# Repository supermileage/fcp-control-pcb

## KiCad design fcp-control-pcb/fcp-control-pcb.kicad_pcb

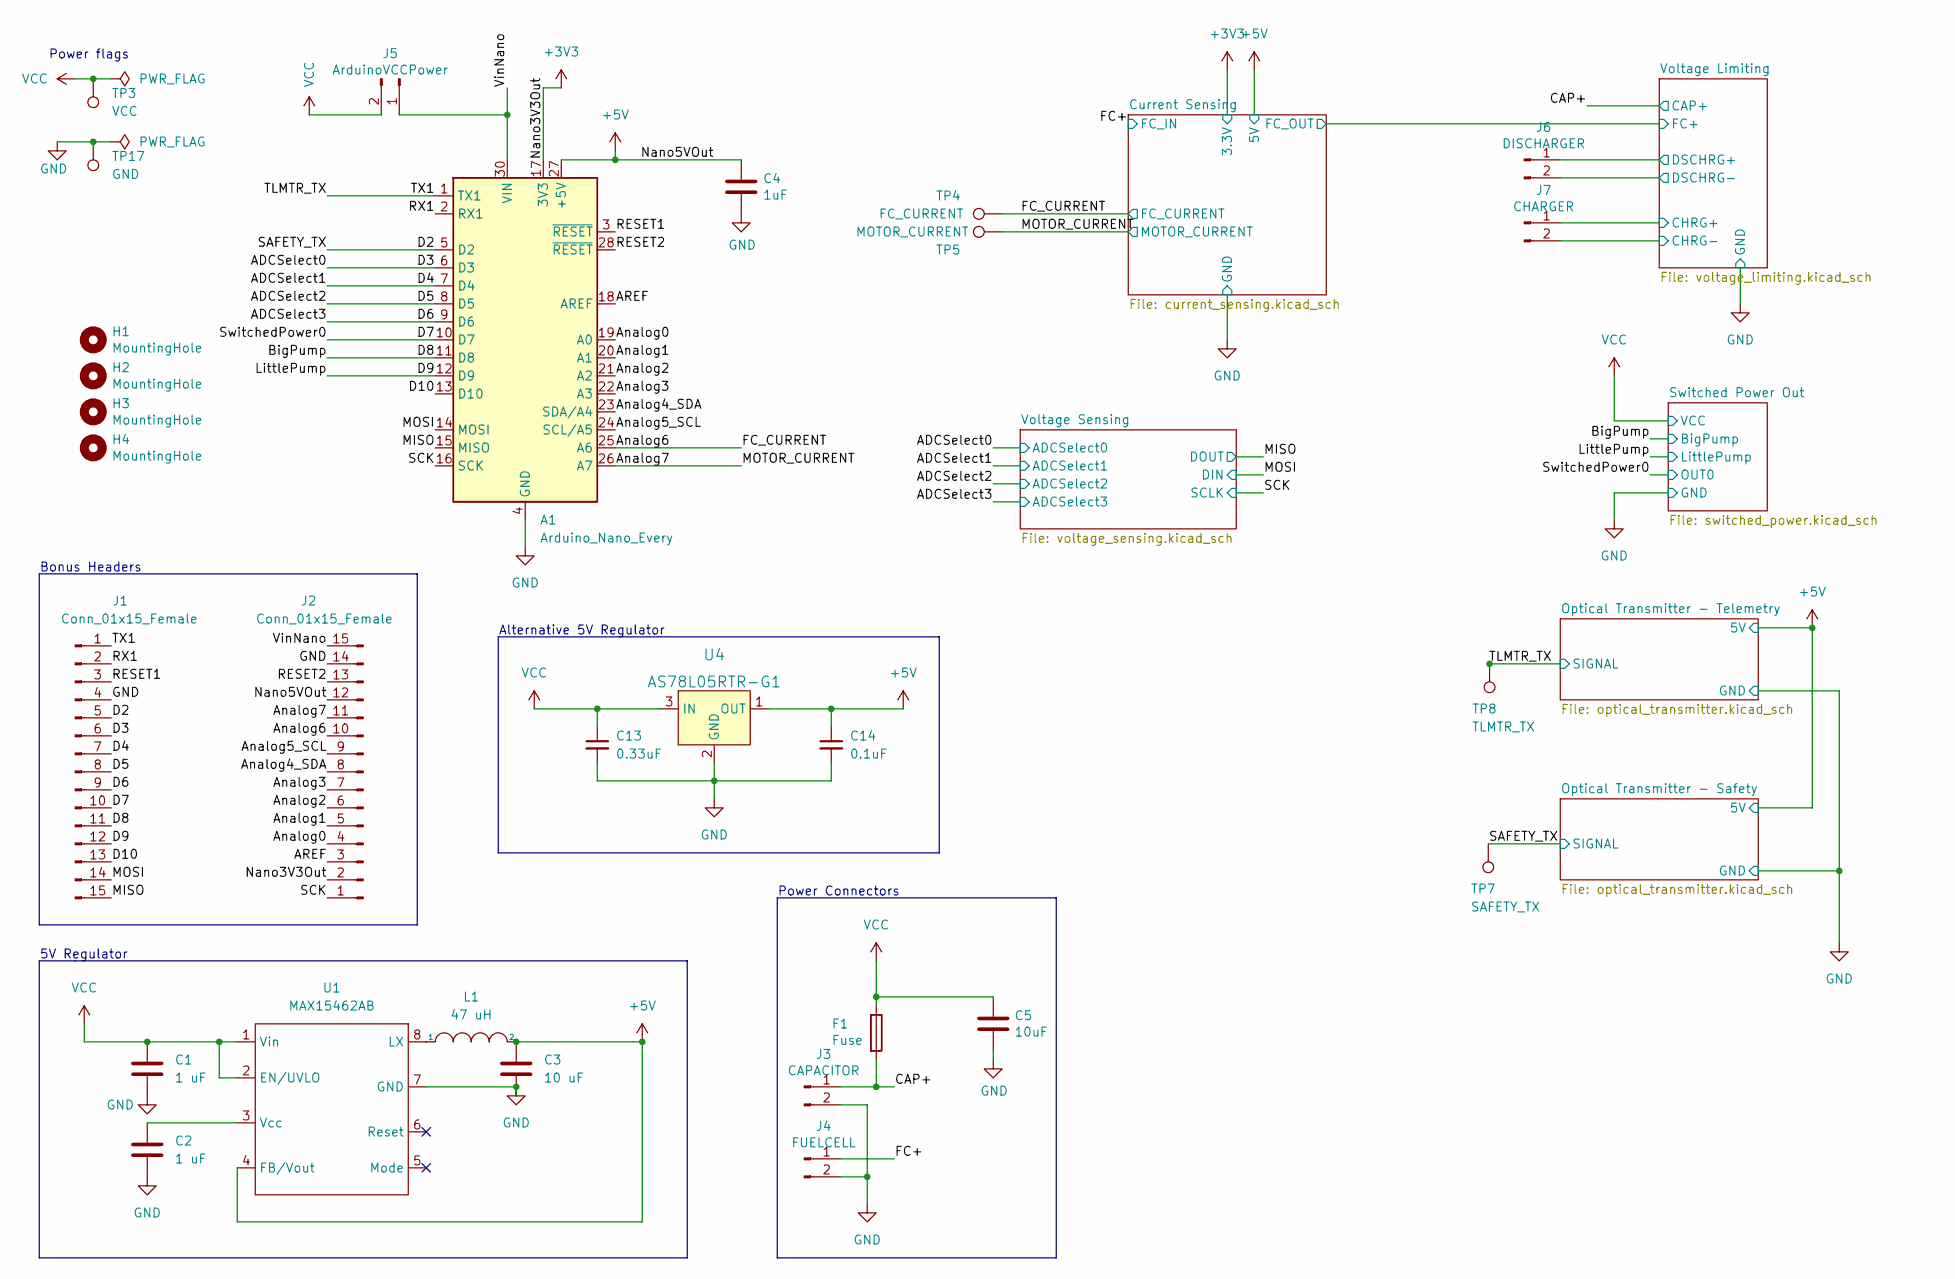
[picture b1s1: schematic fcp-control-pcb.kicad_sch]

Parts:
A1: Arduino_Nano_Every; Arduino_Nano
C1, C2: 1 uF; C_0805_2012Metric_Pad1.18x1.45mm_HandSolder
C3: 10 uF; C_0805_2012Metric_Pad1.18x1.45mm_HandSolder
C4: 1uF; C_0805_2012Metric_Pad1.18x1.45mm_HandSolder; DigikeyPN 490-12330-1-ND
C5: 10uF; C_0805_2012Metric_Pad1.18x1.45mm_HandSolder; DigikeyPN 490-12330-1-ND
C13: 0.33uF; C_0805_2012Metric_Pad1.18x1.45mm_HandSolder
C14: 0.1uF; C_0805_2012Metric_Pad1.18x1.45mm_HandSolder
F1: Fuse; 3586KTR; DigikeyPN 36-3586KCT-ND
H1, H2, H3, H4: MountingHole; MountingHole_3.2mm_M3
J1, J2: Conn_01x15_Female; PinSocket_1x15_P2.54mm_Vertical; MPN 310-87-115-41-001101; DigikeyPN 1212-1103-ND
J3: CAPACITOR; VP0265540000G
J4: FUELCELL; VP0265540000G; DigikeyPN VP0265540000G-ND
J5: ArduinoVCCPower; PinHeader_1x02_P2.54mm_Vertical
J6: DISCHARGER; Molex_Mini-Fit_Jr_5569-02A2_2x01_P4.20mm_Horizontal; DigikeyPN 0050361758-ND
J7: CHARGER; Molex_Mini-Fit_Jr_5569-02A2_2x01_P4.20mm_Horizontal; DigikeyPN 0050361758-ND
L1: 47 uH; L_Coilcraft_LPS4018
TP3: VCC; TestPoint_Pad_4.0x4.0mm
TP4: FC_CURRENT; TestPoint_Pad_4.0x4.0mm
TP5: MOTOR_CURRENT; TestPoint_Pad_4.0x4.0mm
TP7: SAFETY_TX; TestPoint_Pad_4.0x4.0mm
TP8: TLMTR_TX; TestPoint_Pad_4.0x4.0mm
TP17: GND; TestPoint_Pad_4.0x4.0mm
U1: MAX15462AB; TDFN-8-1EP_2x2mm_P0.5mm_EP0.8x1.2mm; digikey part no. MAX15462BATA+TCT-ND
U4: AS78L05RTR-G1; SOT-89-3_Handsoldering; MPN AS78L05RTR-G1; Digi-Key_PN AS78L05RTR-G1DITR-ND

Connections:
+3V3: A1.17 (3V3), J2.2; also elsewhere on the board
+5V: A1.27 (+5V), C3.1, C4.1, C14.1, J2.12, L1.2, U1.4 (FB/Vout), U4.1 (OUT); also elsewhere on the board
/ADCSelect0: A1.6 (D3), J1.6; also elsewhere on the board
/ADCSelect1: A1.7 (D4), J1.7; also elsewhere on the board
/ADCSelect2: A1.8 (D5), J1.8; also elsewhere on the board
/ADCSelect3: A1.9 (D6), J1.9; also elsewhere on the board
/AREF: A1.18 (AREF), J2.3
/Analog0: A1.19 (A0), J2.4
/Analog1: A1.20 (A1), J2.5
/Analog2: A1.21 (A2), J2.6
/Analog3: A1.22 (A3), J2.7
/Analog4_SDA: A1.23 (SDA/A4), J2.8
/Analog5_SCL: A1.24 (SCL/A5), J2.9
/Analog6: A1.25 (A6), J2.10, TP4.1; also elsewhere on the board
/Analog7: A1.26 (A7), J2.11, TP5.1; also elsewhere on the board
/BigPump: A1.11 (D8), J1.11; also elsewhere on the board
/CAP+: F1.2, J3.1; also elsewhere on the board
/D2: A1.5 (D2), J1.5, TP7.1; also elsewhere on the board
/D7: A1.10 (D7), J1.10; also elsewhere on the board
/D9: A1.12 (D9), J1.12; also elsewhere on the board
/D10: A1.13 (D10), J1.13
/FC+: J4.1; also elsewhere on the board
/MISO: A1.15 (MISO), J1.15; also elsewhere on the board
/MOSI: A1.14 (MOSI), J1.14; also elsewhere on the board
/RESET1: A1.3 (~RESET), J1.3
/RESET2: A1.28 (~RESET), J2.13
/RX1: A1.2 (RX1), J1.2
/SCK: A1.16 (SCK), J2.1; also elsewhere on the board
/TLMTR_TX: A1.1 (TX1), J1.1, TP8.1; also elsewhere on the board
/VinNano: A1.30 (VIN), J2.15, J5.1
/Voltage Limiting/CHRG+: J7.1; also elsewhere on the board
/Voltage Limiting/DSCHRG+: J6.1; also elsewhere on the board
GND: A1.4 (GND), A1.29 (GND), C1.2, C2.2, C3.2, C4.2, C5.2, C13.2, C14.2, J1.4, J2.14, J3.2, J4.2, J6.2, J7.2, TP17.1, U1.7 (GND), U4.2 (GND); also elsewhere on the board
unnamed: C2.1, U1.3 (Vcc)
unnamed: L1.1, U1.8 (LX)
VCC: C1.1, C5.1, C13.1, F1.1, J5.2, TP3.1, U1.1 (Vin), U1.2 (EN/UVLO), U4.3 (IN); also elsewhere on the board

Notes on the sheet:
5V Regulator
Power Connectors
Power flags
Bonus Headers
Alternative 5V Regulator

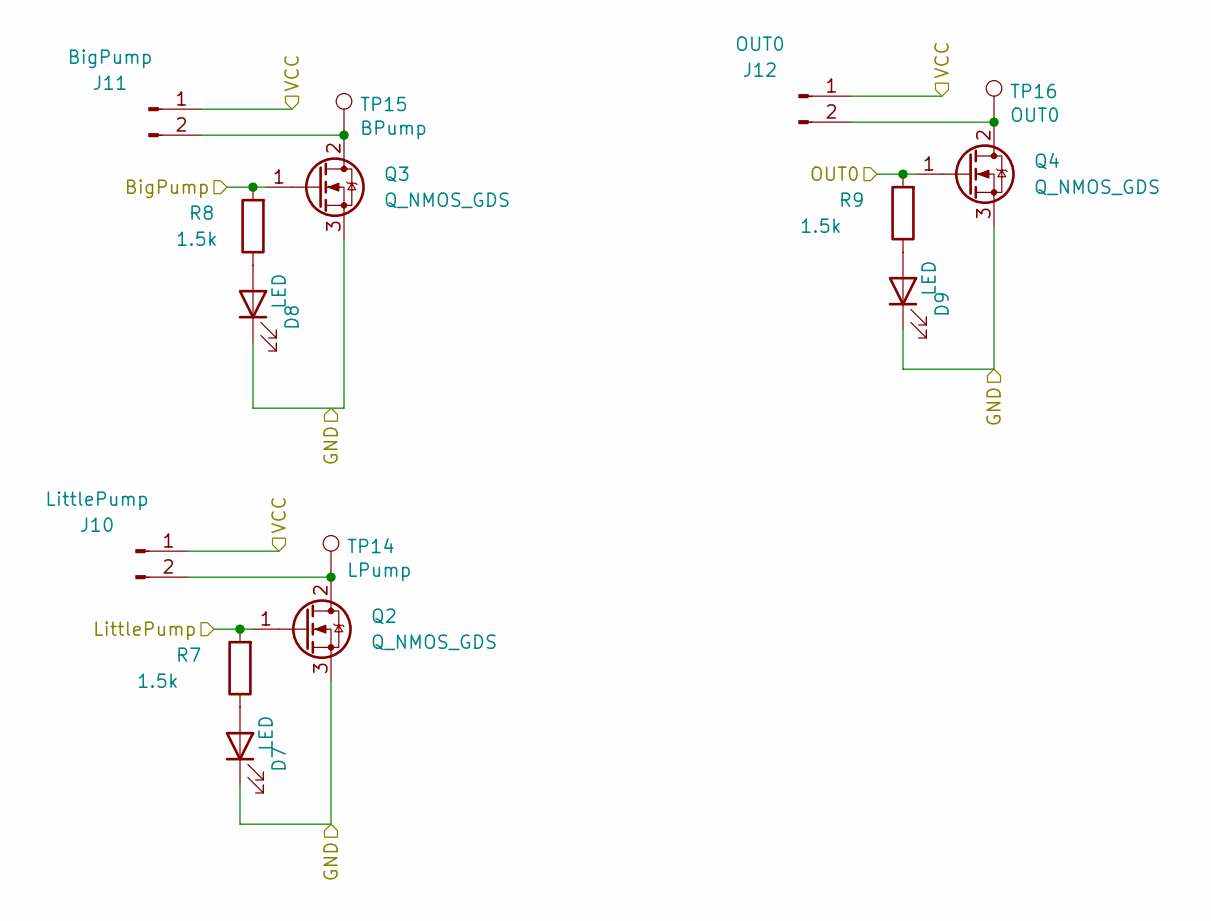
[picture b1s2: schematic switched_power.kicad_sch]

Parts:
D7, D8, D9: LED; LED_0603_1608Metric; DigikeyPN SML-D12W8WT86ACT-ND
J10: LittlePump; Molex_Mini-Fit_Jr_5569-02A2_2x01_P4.20mm_Horizontal; DigikeyPN 0050361758-ND
J11: BigPump; Molex_Mini-Fit_Jr_5569-02A2_2x01_P4.20mm_Horizontal; DigikeyPN 0050361758-ND
J12: OUT0; Molex_Mini-Fit_Jr_5569-02A2_2x01_P4.20mm_Horizontal; DigikeyPN 0050361758-ND
Q2, Q3, Q4: Q_NMOS_GDS; SOT-89-3_Handsoldering; DigikeyPN DMN2004WKDICT-ND
R7, R8, R9: 1.5k; R_0805_2012Metric_Pad1.20x1.40mm_HandSolder; DigikeyPN A121524CT-ND
TP14: LPump; PinSocket_1x01_P2.54mm_Vertical
TP15: BPump; PinSocket_1x01_P2.54mm_Vertical
TP16: OUT0; PinSocket_1x01_P2.54mm_Vertical

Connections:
/BigPump: Q3.1 (G), R8.2; also elsewhere on the board
/D7: Q4.1 (G), R9.2; also elsewhere on the board
/D9: Q2.1 (G), R7.2; also elsewhere on the board
GND: D7.1 (K), D8.1 (K), D9.1 (K), Q2.3 (S), Q3.3 (S), Q4.3 (S); also elsewhere on the board
unnamed: D7.2 (A), R7.1
unnamed: D8.2 (A), R8.1
unnamed: D9.2 (A), R9.1
unnamed: J10.2, Q2.2 (D), TP14.1
unnamed: J11.2, Q3.2 (D), TP15.1
unnamed: J12.2, Q4.2 (D), TP16.1
VCC: J10.1, J11.1, J12.1; also elsewhere on the board

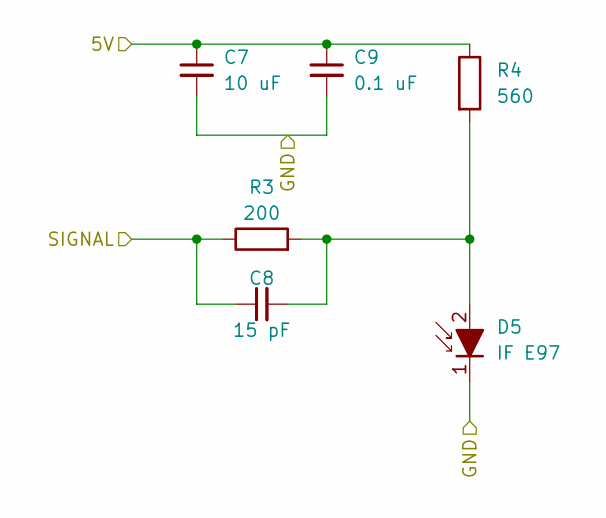
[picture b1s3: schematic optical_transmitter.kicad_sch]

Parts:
C7: 10 uF; C_0805_2012Metric_Pad1.18x1.45mm_HandSolder
C8: 15 pF; C_0805_2012Metric_Pad1.18x1.45mm_HandSolder
C9: 0.1 uF; C_0805_2012Metric_Pad1.18x1.45mm_HandSolder
D5: IF E97; IF-E97
R3: 200; R_0805_2012Metric_Pad1.20x1.40mm_HandSolder
R4: 560; R_0805_2012Metric_Pad1.20x1.40mm_HandSolder

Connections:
+5V: C7.1, C9.1, R4.1; also elsewhere on the board
/TLMTR_TX: C8.1, R3.1; also elsewhere on the board
GND: C7.2, C9.2, D5.1 (K); also elsewhere on the board
unnamed: C8.2, D5.2 (A), R3.2, R4.2

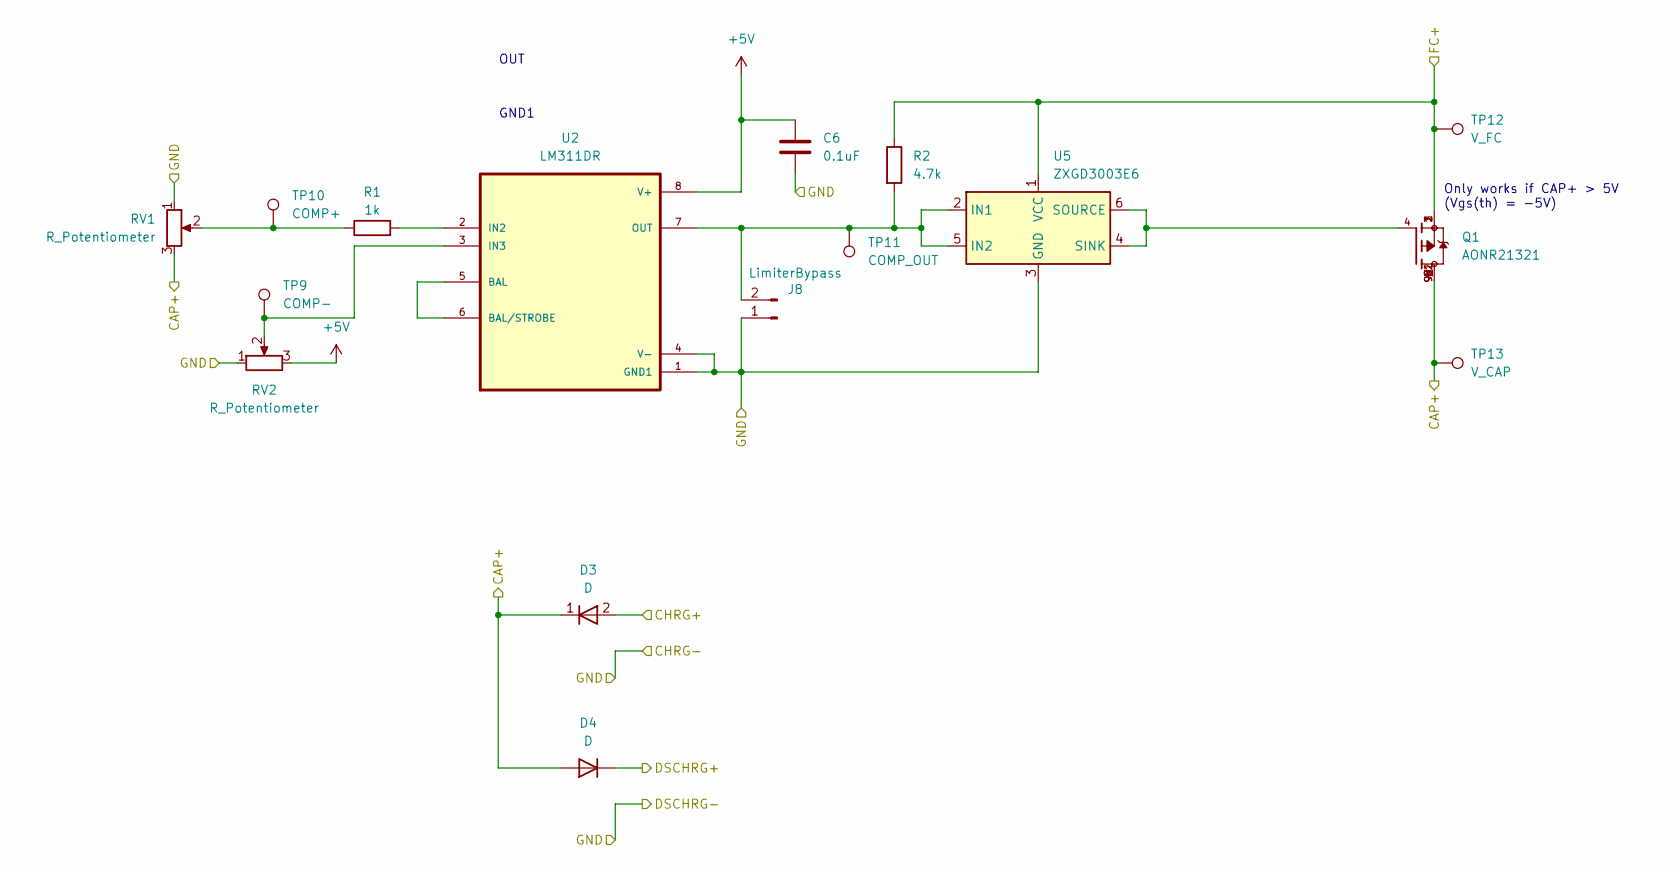
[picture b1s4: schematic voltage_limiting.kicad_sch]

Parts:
C6: 0.1uF; C_0805_2012Metric_Pad1.18x1.45mm_HandSolder
D3, D4: D; D_PowerDI-5
J8: LimiterBypass; PinHeader_1x02_P2.54mm_Vertical; DigikeyPN 0050361758-ND
Q1: AONR21321; TRANS_AONR21321; PARTREV 1.0
R1: 1k; R_0805_2012Metric_Pad1.20x1.40mm_HandSolder
R2: 4.7k; R_0805_2012Metric_Pad1.20x1.40mm_HandSolder
RV1, RV2: R_Potentiometer; TRIM_3361P-1-203GLF
TP9: COMP-; TestPoint_Pad_4.0x4.0mm
TP10: COMP+; TestPoint_Pad_4.0x4.0mm
TP11: COMP_OUT; TestPoint_Pad_4.0x4.0mm
TP12: V_FC; TestPoint_Pad_4.0x4.0mm
TP13: V_CAP; TestPoint_Pad_4.0x4.0mm
U2: LM311DR; SOIC127P599X175-8N
U5: ZXGD3003E6; SOT-23-6

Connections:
+5V: C6.1, RV2.3, U2.8 (V+); also elsewhere on the board
/CAP+: D3.1 (K), D4.2 (A), Q1.5, Q1.6, Q1.7, Q1.8, Q1.9, Q1.9_1, Q1.9_2, RV1.3, TP13.1; also elsewhere on the board
/Current Sensing/FC_OUT: Q1.1, Q1.2, Q1.3, R2.1, TP12.1, U5.1 (VCC); also elsewhere on the board
/Voltage Limiting/CHRG+: D3.2 (A); also elsewhere on the board
/Voltage Limiting/DSCHRG+: D4.1 (K); also elsewhere on the board
GND: C6.2, J8.1, RV1.1, RV2.1, U2.1 (GND1), U2.4 (V-), U5.3 (GND); also elsewhere on the board
unnamed: J8.2, R2.2, TP11.1, U2.7 (OUT), U5.2 (IN1), U5.5 (IN2)
unnamed: Q1.4, U5.4 (SINK), U5.6 (SOURCE)
unnamed: R1.1, RV1.2, TP10.1
unnamed: R1.2, U2.2 (IN2)
unnamed: RV2.2, TP9.1, U2.3 (IN3)
unnamed: U2.5 (BAL), U2.6 (BAL/STROBE)

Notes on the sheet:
OUT
GND1
Only works if CAP+ > 5V (Vgs(th) = -5V)

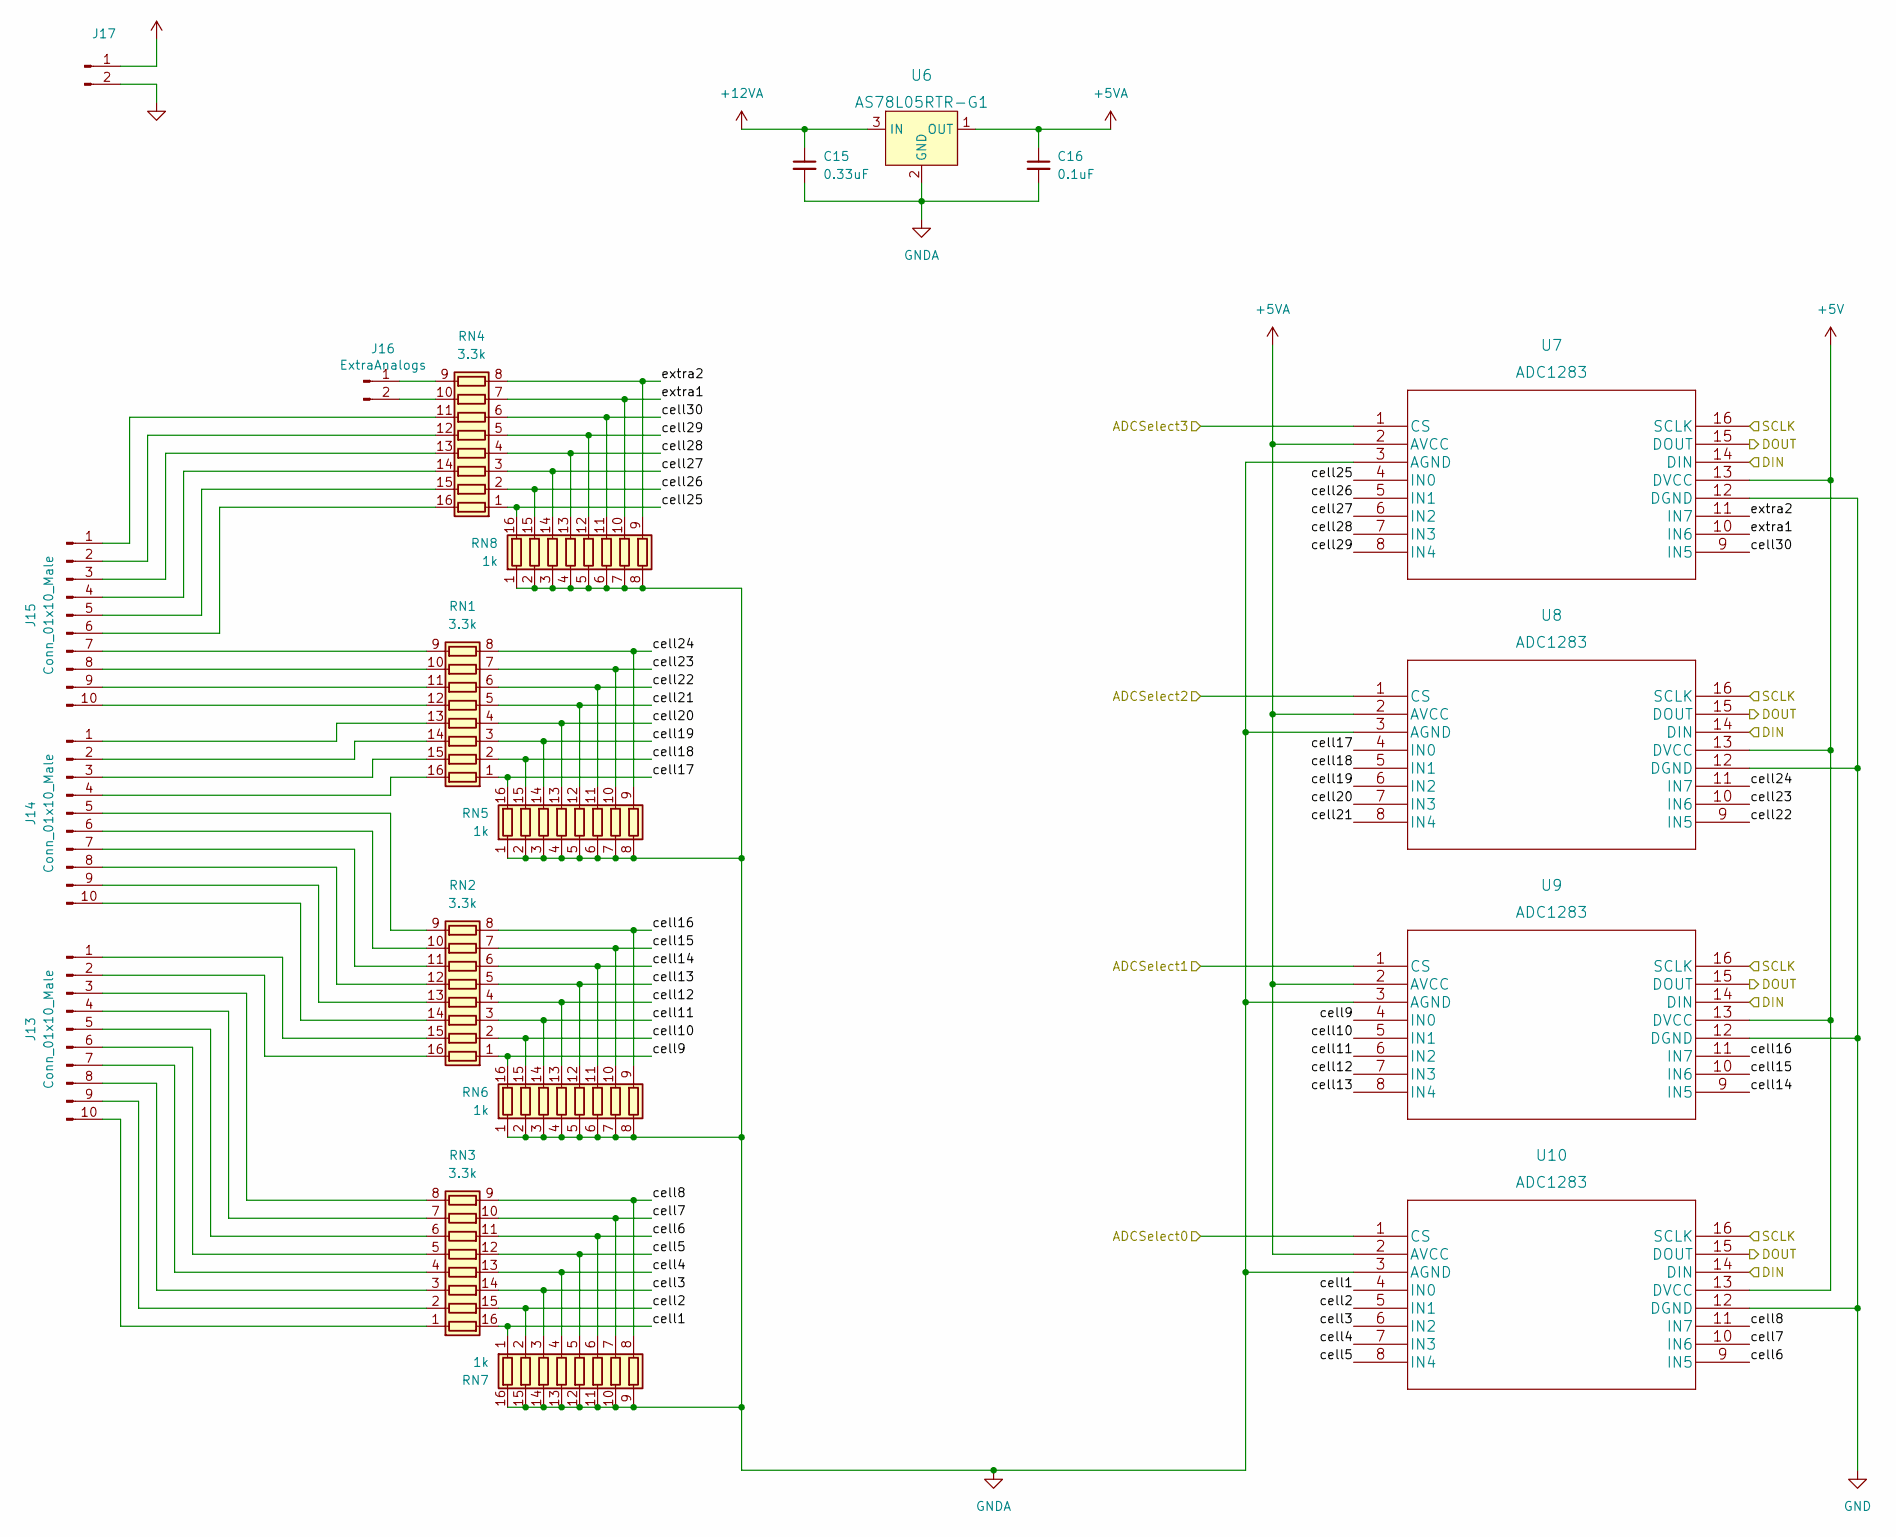
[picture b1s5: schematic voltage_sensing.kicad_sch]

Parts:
C15: 0.33uF; C_0805_2012Metric_Pad1.18x1.45mm_HandSolder
C16: 0.1uF; C_0805_2012Metric_Pad1.18x1.45mm_HandSolder
J13, J14, J15: Conn_01x10_Male; PhoenixContact_MCV_1,5_10-G-3.5_1x10_P3.50mm_Vertical; DigikeyPN 277-5774-ND
J16: ExtraAnalogs; PinHeader_1x02_P2.54mm_Vertical
J17: DigikeyPN 0050361758-ND
RN1, RN2, RN3, RN4: 3.3k; SOIC-16_4.55x10.3mm_P1.27mm
RN5, RN6, RN7, RN8: 1k; SOIC-16_4.55x10.3mm_P1.27mm
U6: AS78L05RTR-G1; SOT-89-3_Handsoldering; MPN AS78L05RTR-G1; Digi-Key_PN AS78L05RTR-G1DITR-ND
U7, U8, U9, U10: ADC1283; TSSOP-16_4.4x5mm_P0.65mm

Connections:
+5V: U7.13 (DVCC), U8.13 (DVCC), U9.13 (DVCC), U10.13 (DVCC); also elsewhere on the board
+5VA: C16.1, U6.1 (OUT), U7.2 (AVCC), U8.2 (AVCC), U9.2 (AVCC), U10.2 (AVCC)
/ADCSelect0: U10.1 (CS); also elsewhere on the board
/ADCSelect1: U9.1 (CS); also elsewhere on the board
/ADCSelect2: U8.1 (CS); also elsewhere on the board
/ADCSelect3: U7.1 (CS); also elsewhere on the board
/MISO: U7.15 (DOUT), U8.15 (DOUT), U9.15 (DOUT), U10.15 (DOUT); also elsewhere on the board
/MOSI: U7.14 (DIN), U8.14 (DIN), U9.14 (DIN), U10.14 (DIN); also elsewhere on the board
/SCK: U7.16 (SCLK), U8.16 (SCLK), U9.16 (SCLK), U10.16 (SCLK); also elsewhere on the board
/Voltage Sensing/cell1: RN3.16 (R1.2), RN7.1 (R1.1), U10.4 (IN0)
/Voltage Sensing/cell2: RN3.15 (R2.2), RN7.2 (R2.1), U10.5 (IN1)
/Voltage Sensing/cell3: RN3.14 (R3.2), RN7.3 (R3.1), U10.6 (IN2)
/Voltage Sensing/cell4: RN3.13 (R4.2), RN7.4 (R4.1), U10.7 (IN3)
/Voltage Sensing/cell5: RN3.12 (R5.2), RN7.5 (R5.1), U10.8 (IN4)
/Voltage Sensing/cell6: RN3.11 (R6.2), RN7.6 (R6.1), U10.9 (IN5)
/Voltage Sensing/cell7: RN3.10 (R7.2), RN7.7 (R7.1), U10.10 (IN6)
/Voltage Sensing/cell8: RN3.9 (R8.2), RN7.8 (R8.1), U10.11 (IN7)
/Voltage Sensing/cell9: RN2.1 (R1.1), RN6.16 (R1.2), U9.4 (IN0)
/Voltage Sensing/cell10: RN2.2 (R2.1), RN6.15 (R2.2), U9.5 (IN1)
/Voltage Sensing/cell11: RN2.3 (R3.1), RN6.14 (R3.2), U9.6 (IN2)
/Voltage Sensing/cell12: RN2.4 (R4.1), RN6.13 (R4.2), U9.7 (IN3)
/Voltage Sensing/cell13: RN2.5 (R5.1), RN6.12 (R5.2), U9.8 (IN4)
/Voltage Sensing/cell14: RN2.6 (R6.1), RN6.11 (R6.2), U9.9 (IN5)
/Voltage Sensing/cell15: RN2.7 (R7.1), RN6.10 (R7.2), U9.10 (IN6)
/Voltage Sensing/cell16: RN2.8 (R8.1), RN6.9 (R8.2), U9.11 (IN7)
/Voltage Sensing/cell17: RN1.1 (R1.1), RN5.16 (R1.2), U8.4 (IN0)
/Voltage Sensing/cell18: RN1.2 (R2.1), RN5.15 (R2.2), U8.5 (IN1)
/Voltage Sensing/cell19: RN1.3 (R3.1), RN5.14 (R3.2), U8.6 (IN2)
/Voltage Sensing/cell20: RN1.4 (R4.1), RN5.13 (R4.2), U8.7 (IN3)
/Voltage Sensing/cell21: RN1.5 (R5.1), RN5.12 (R5.2), U8.8 (IN4)
/Voltage Sensing/cell22: RN1.6 (R6.1), RN5.11 (R6.2), U8.9 (IN5)
/Voltage Sensing/cell23: RN1.7 (R7.1), RN5.10 (R7.2), U8.10 (IN6)
/Voltage Sensing/cell24: RN1.8 (R8.1), RN5.9 (R8.2), U8.11 (IN7)
/Voltage Sensing/cell25: RN4.1 (R1.1), RN8.16 (R1.2), U7.4 (IN0)
/Voltage Sensing/cell26: RN4.2 (R2.1), RN8.15 (R2.2), U7.5 (IN1)
/Voltage Sensing/cell27: RN4.3 (R3.1), RN8.14 (R3.2), U7.6 (IN2)
/Voltage Sensing/cell28: RN4.4 (R4.1), RN8.13 (R4.2), U7.7 (IN3)
/Voltage Sensing/cell29: RN4.5 (R5.1), RN8.12 (R5.2), U7.8 (IN4)
/Voltage Sensing/cell30: RN4.6 (R6.1), RN8.11 (R6.2), U7.9 (IN5)
/Voltage Sensing/extra1: RN4.7 (R7.1), RN8.10 (R7.2), U7.10 (IN6)
/Voltage Sensing/extra2: RN4.8 (R8.1), RN8.9 (R8.2), U7.11 (IN7)
GND: U7.12 (DGND), U8.12 (DGND), U9.12 (DGND), U10.12 (DGND); also elsewhere on the board
unnamed: J13.1, RN2.15 (R2.2)
unnamed: J13.2, RN2.16 (R1.2)
unnamed: J13.3, RN3.8 (R8.1)
unnamed: J13.4, RN3.7 (R7.1)
unnamed: J13.5, RN3.6 (R6.1)
unnamed: J13.6, RN3.5 (R5.1)
unnamed: J13.7, RN3.4 (R4.1)
unnamed: J13.8, RN3.3 (R3.1)
unnamed: J13.9, RN3.2 (R2.1)
unnamed: J13.10, RN3.1 (R1.1)
unnamed: J14.1, RN1.13 (R4.2)
unnamed: J14.2, RN1.14 (R3.2)
unnamed: J14.3, RN1.15 (R2.2)
unnamed: J14.4, RN1.16 (R1.2)
unnamed: J14.5, RN2.9 (R8.2)
unnamed: J14.6, RN2.10 (R7.2)
unnamed: J14.7, RN2.11 (R6.2)
unnamed: J14.8, RN2.12 (R5.2)
unnamed: J14.9, RN2.13 (R4.2)
unnamed: J14.10, RN2.14 (R3.2)
unnamed: J15.1, RN4.11 (R6.2)
unnamed: J15.2, RN4.12 (R5.2)
unnamed: J15.3, RN4.13 (R4.2)
unnamed: J15.4, RN4.14 (R3.2)
unnamed: J15.5, RN4.15 (R2.2)
unnamed: J15.6, RN4.16 (R1.2)
unnamed: J15.7, RN1.9 (R8.2)
unnamed: J15.8, RN1.10 (R7.2)
unnamed: J15.9, RN1.11 (R6.2)
unnamed: J15.10, RN1.12 (R5.2)
unnamed: J16.1, RN4.9 (R8.2)
unnamed: J16.2, RN4.10 (R7.2)

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
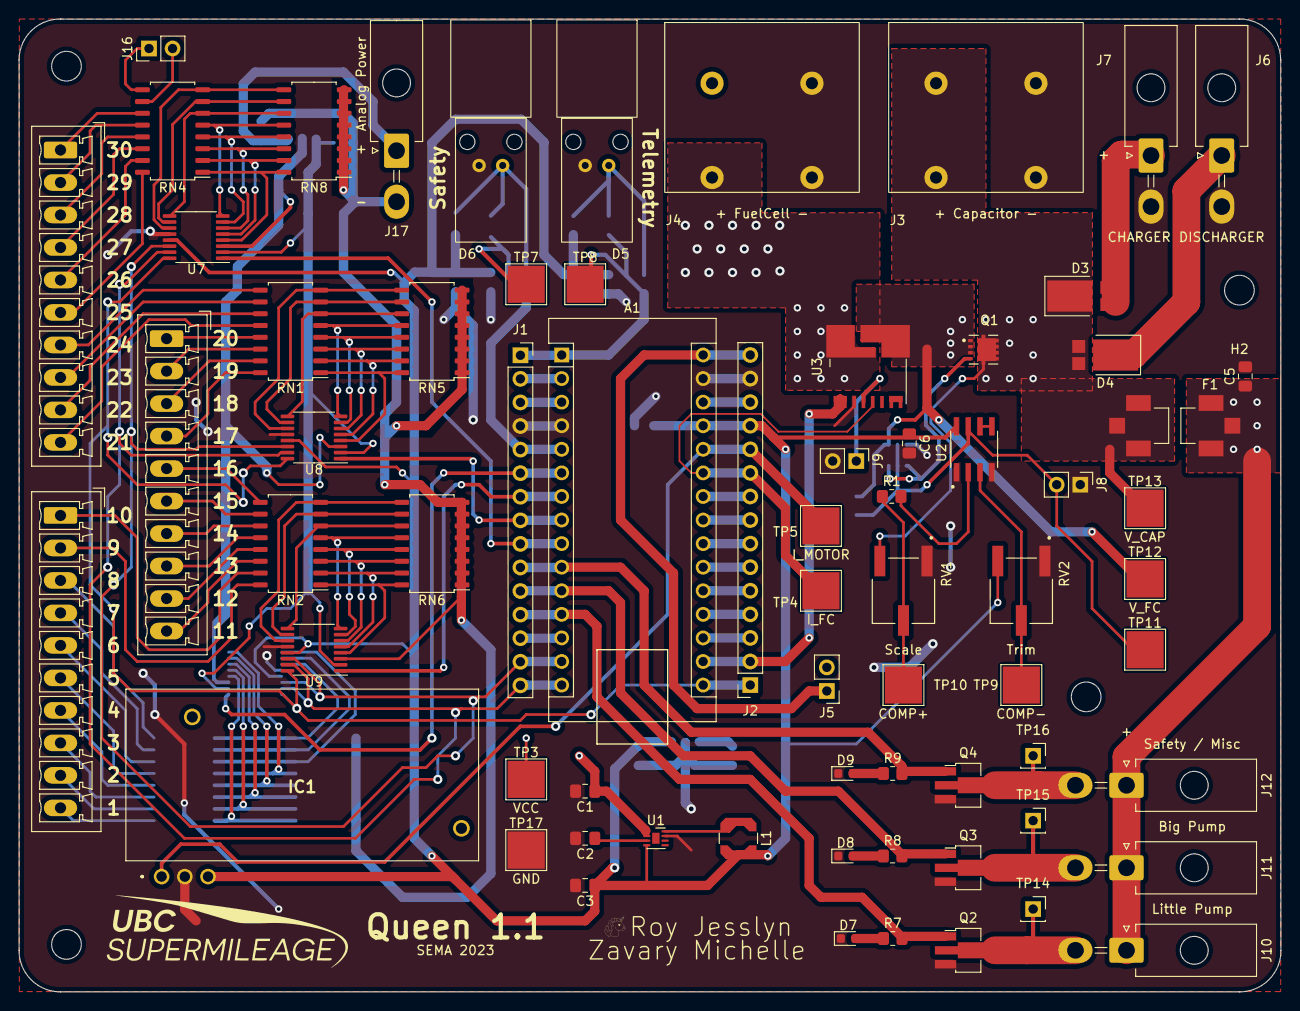
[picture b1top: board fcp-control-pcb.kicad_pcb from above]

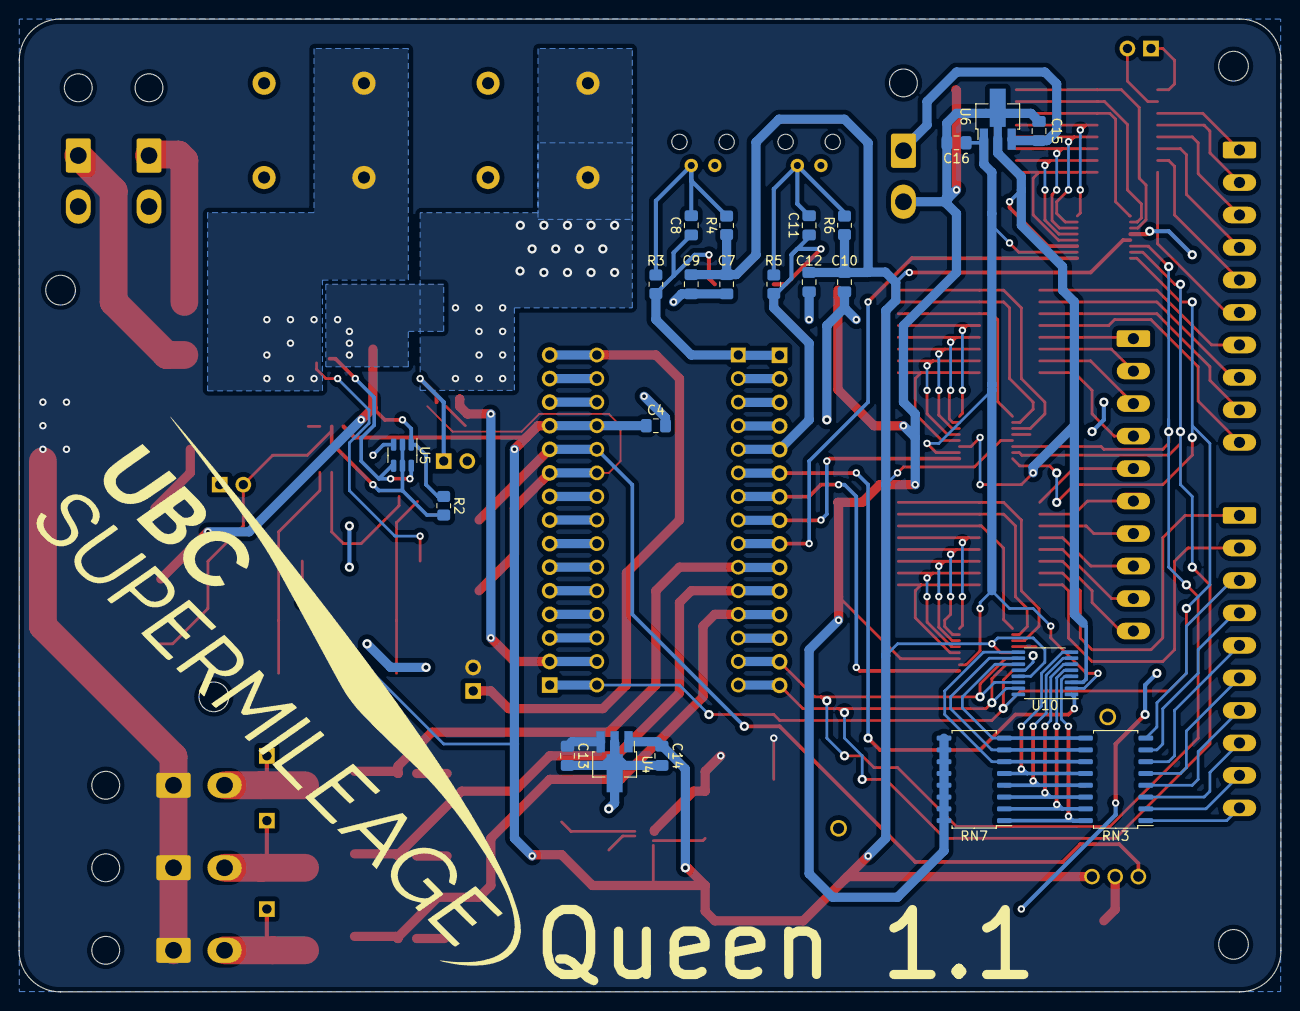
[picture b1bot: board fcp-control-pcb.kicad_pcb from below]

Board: 2 copper layers, 136.0 x 104.8 mm, 95 parts (22 on the bottom side), 119 nets.

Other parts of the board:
C10: 10 uF; C_0805_2012Metric_Pad1.18x1.45mm_HandSolder
C11: 15 pF; C_0805_2012Metric_Pad1.18x1.45mm_HandSolder
C12: 0.1 uF; C_0805_2012Metric_Pad1.18x1.45mm_HandSolder
D6: IF E97; IF-E97
IC1: L01Z050S05
J9: Current_Mode; PinHeader_1x02_P2.54mm_Vertical
R5: 200; R_0805_2012Metric_Pad1.20x1.40mm_HandSolder
R6: 560; R_0805_2012Metric_Pad1.20x1.40mm_HandSolder
U3: TLI4971-A050T5-U-E0001; Infineon_PG-TISON-8-5

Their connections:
+3V3: U3.1 (VDD); also elsewhere on the board
+5V: C10.1, C12.1, IC1.3 (+VCC_(+5V)), R6.1; also elsewhere on the board
/Analog6: U3.4 (Aout); also elsewhere on the board
/Analog7: IC1.1 (VOUT); also elsewhere on the board
/Current Sensing/FC_OUT: U3.7 (IP-); also elsewhere on the board
/D2: C11.1, R5.1; also elsewhere on the board
/FC+: U3.8 (IP+); also elsewhere on the board
GND: C10.2, C12.2, D6.1 (K), IC1.2 (GND), J9.2, U3.2 (GND); also elsewhere on the board
unnamed: C11.2, D6.2 (A), R5.2, R6.2
unnamed: J9.1, U3.3 (VREF)

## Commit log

2022-12-03 Design without voltage monitoring
2023-01-12 pcb sans design review
2023-01-12 adds vias to fcc fuse
2023-01-12 layout changes
2023-01-12 silscreen
2023-01-14 adds enable pin control to multiplexers
2023-01-14 fixed overlapping silkscreen
2023-02-27 queen r1.1
2023-02-27 resize board
2023-02-27 label tps
2023-03-04 updated schematic and pcb for queen 1.1
2023-03-04 Fixed autosave issues
2023-03-18 Queen 1.1
2023-03-19 git pull new schematic
